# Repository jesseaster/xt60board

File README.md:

XT60 Board
----------

This is a XT60 Board with 12 connectors designed using KiCad.

The Gerber folder contains the files to send to the PCB Manufacturer.

<div style="text-align:center;">

</div>

License
-------

This board is released under the MIT License.

Credit for the XT60.kicad_mod goes to https://pappkopp.com/?p=222

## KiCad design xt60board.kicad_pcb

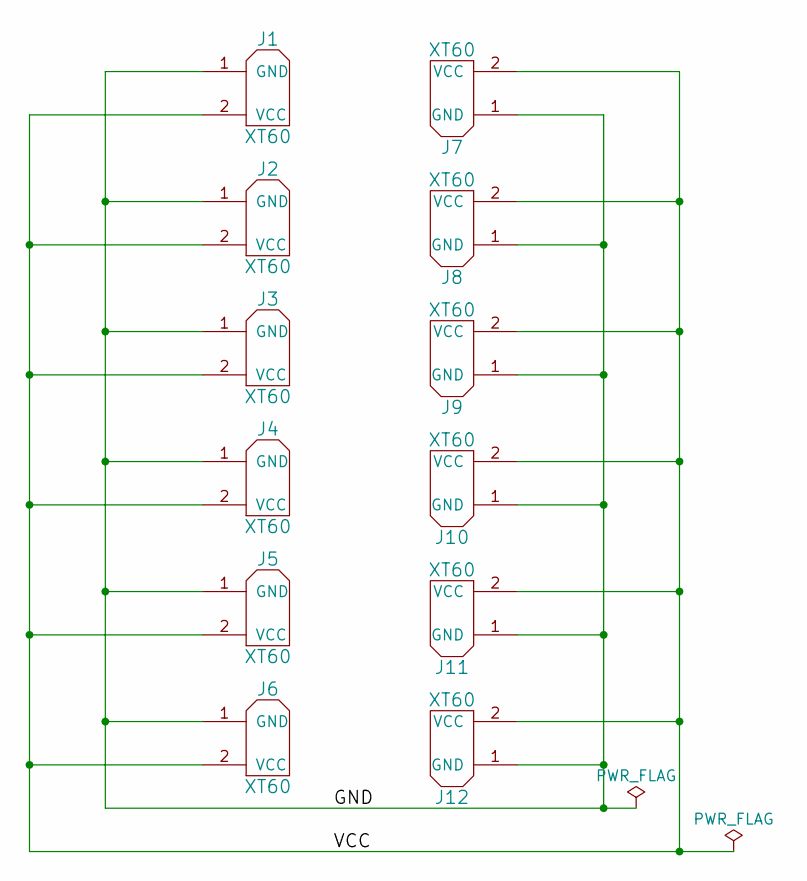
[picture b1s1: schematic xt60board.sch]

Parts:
J1, J2, J3, J4, J5, J6, J7, J8, J9, J10, J11, J12: XT60

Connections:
/GND: J1.1 (GND), J2.1 (GND), J3.1 (GND), J4.1 (GND), J5.1 (GND), J6.1 (GND), J7.1 (GND), J8.1 (GND), J9.1 (GND), J10.1 (GND), J11.1 (GND), J12.1 (GND)
/VCC: J1.2 (VCC), J2.2 (VCC), J3.2 (VCC), J4.2 (VCC), J5.2 (VCC), J6.2 (VCC), J7.2 (VCC), J8.2 (VCC), J9.2 (VCC), J10.2 (VCC), J11.2 (VCC), J12.2 (VCC)

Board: 2 copper layers, 12 parts (0 on the bottom side), 2 nets, no tracks yet.

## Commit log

2017-09-12 Version 1 of XT60 Board
2017-09-12 Added Render
2017-09-12 Version 2
    Shrank board size to reduce manufacturing cost.
2017-09-12 Moved Gerber files to Gerber directory
